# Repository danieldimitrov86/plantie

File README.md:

# Plantie: ESP32 Low-Power Plant Monitor

A complete open-source ecosystem for smart plant monitoring. This project consists of a battery-powered, low-energy **Control Unit** that interfaces with a soil moisture sensor, and a dedicated **Base Station** for charging and data upload.

## 🚧 Project Status

This project is currently under active development.

- [X] **Control Unit:** Hardware Schematics
- [ ] **Control Unit:** PCB Layout
- [ ] **Control Unit:** Firmware
- [ ] **Control Unit:** 3D Printable Enclosure Design
- [X] **Base Station:** Hardware Schematics
- [ ] **Base Station:** PCB Layout
- [ ] **Base Station:** 3D Printable Enclosure Design

## 📂 Repository Structure

```text
.
├── firmware/              # Source code for the ESP32 Control Unit
│   └── control-unit/      # Code for the main module
│
├── hardware/              # PCB Design files (KiCad)
│   ├── base-station/      # (WIP) Schematic & layout for the dock
│   └── control-unit/      # Schematic & layout for the main module
│
└── mechanical/            # (WIP) 3D models for enclosures

```

## ⚖️ License

This project is dual-licensed to accommodate both hardware and software freedoms:

### 🖥️ Software (Firmware)

All code located in the `firmware/` directory is licensed under a [GNU General Public License v3.0 (GPL-3.0)](LICENSE-GPL).

### 🛠️ Hardware (Schematics, PCB, 3D Models)
[![CC BY-SA 4.0][cc-by-sa-shield]][cc-by-sa]

All hardware designs located in the `hardware/` directory are licensed under a
[Creative Commons Attribution-ShareAlike 4.0 International License][cc-by-sa].

[![CC BY-SA 4.0][cc-by-sa-image]][cc-by-sa]

[cc-by-sa]: http://creativecommons.org/licenses/by-sa/4.0/
[cc-by-sa-image]: https://licensebuttons.net/l/by-sa/4.0/88x31.png
[cc-by-sa-shield]: https://img.shields.io/badge/License-CC%20BY--SA%204.0-lightgrey.svg

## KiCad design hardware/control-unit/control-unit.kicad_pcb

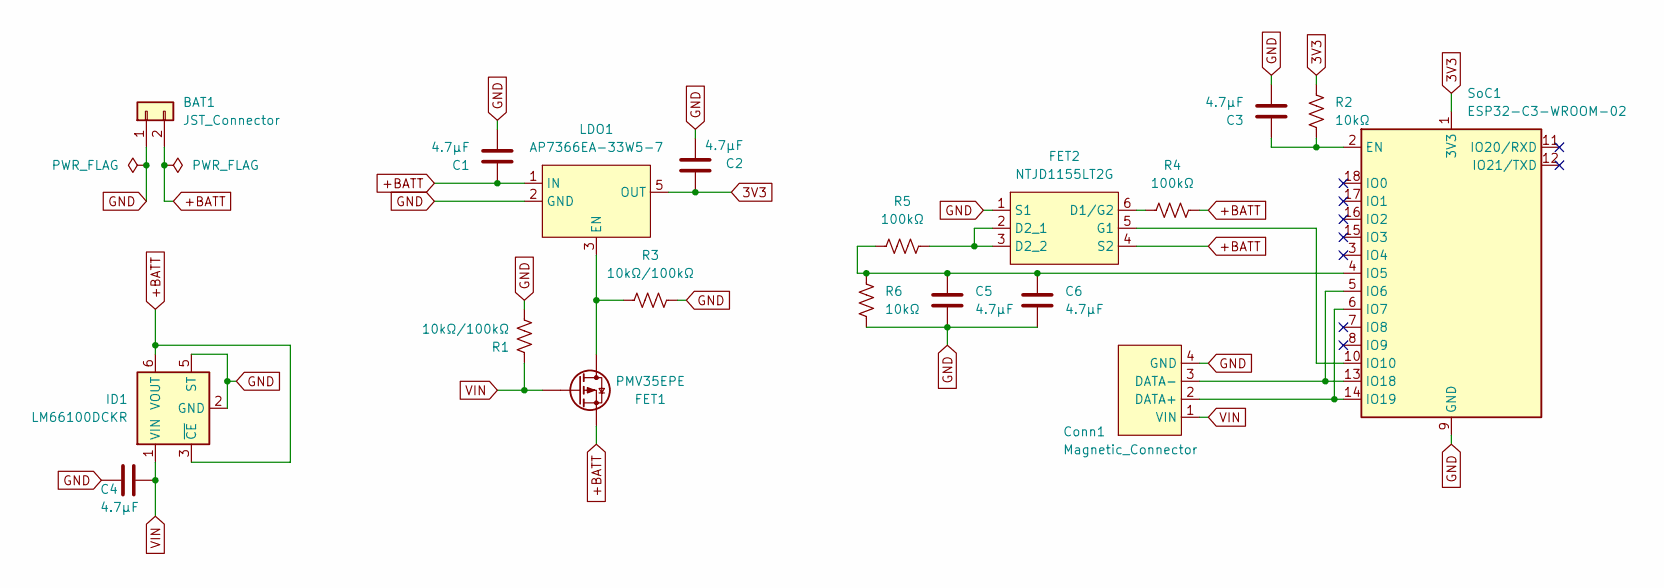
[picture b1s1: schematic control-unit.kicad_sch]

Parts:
BAT1: JST_Connector; JST_EH_B2B-EH-A_1x02_P2.50mm_Vertical
C1, C2, C3, C4, C5, C6: 4.7µF; C_0402_1005Metric_Pad0.74x0.62mm_HandSolder
Conn1: Magnetic_Connector; Connector_Magnetic_4_Pin
FET1: PMV35EPE; SOT-23_Handsoldering
FET2: NTJD1155LT2G; SOT-363_SC-70-6_Handsoldering
ID1: LM66100DCKR; SOT-363_SC-70-6_Handsoldering
LDO1: AP7366EA-33W5-7; SOT-23-5_HandSoldering
R1, R3: 10kΩ/100kΩ; R_0805_2012Metric_Pad1.20x1.40mm_HandSolder
R2, R6: 10kΩ; R_0805_2012Metric_Pad1.20x1.40mm_HandSolder
R4, R5: 100kΩ; R_0805_2012Metric_Pad1.20x1.40mm_HandSolder
SoC1: ESP32-C3-WROOM-02; ESP32-C3-WROOM-02_Handsolder

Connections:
+3.3V: C2.2, LDO1.5 (OUT), R2.2, SoC1.1 (3V3)
+BATT: BAT1.2, C1.2, FET1.2 (S), FET2.4 (S2), ID1.3 (~CE), ID1.6 (VOUT), LDO1.1 (IN), R4.2
GND: BAT1.1, C1.1, C2.1, C3.1, C4.1, C5.1, C6.1, Conn1.4 (GND), FET2.1 (S1), ID1.2 (GND), ID1.5 (ST), LDO1.2 (GND), R1.1, R3.2, R6.1, SoC1.9 (GND), SoC1.19 (GND)
unnamed: Conn1.2 (DATA+), SoC1.6 (IO7), SoC1.14 (IO19)
unnamed: Conn1.3 (DATA-), SoC1.5 (IO6), SoC1.13 (IO18)
unnamed: FET1.3 (D), LDO1.3 (EN), R3.1
unnamed: FET2.6 (D1/G2), R4.1
unnamed: FET2.2 (D2_1), FET2.3 (D2_2), R5.2
unnamed: FET2.5 (G1), SoC1.10 (IO10)
unnamed: C3.2, R2.1, SoC1.2 (EN)
unnamed: C5.2, C6.2, R5.1, R6.2, SoC1.4 (IO5)
VIN: C4.2, Conn1.1 (VIN), FET1.1 (G), ID1.1 (VIN), R1.2

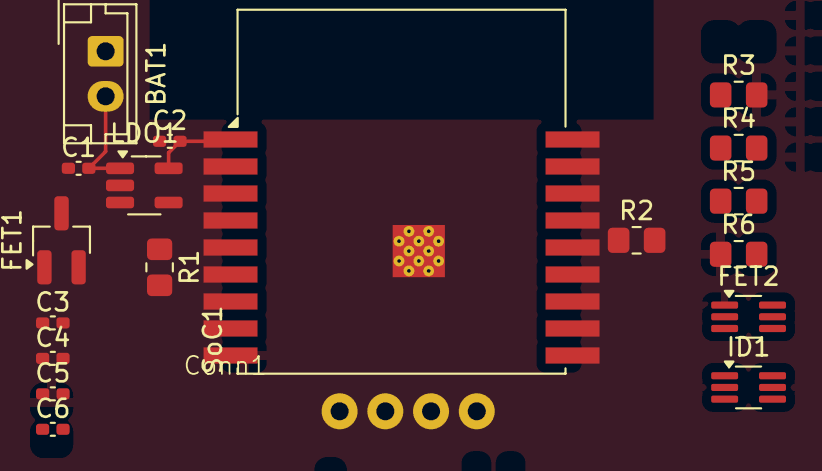
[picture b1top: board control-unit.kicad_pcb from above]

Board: 2 copper layers, 19 parts (0 on the bottom side), 12 nets.

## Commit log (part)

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2025-11-25 Imported KiCad projects for control unit and base station. Added README.md and CC license.
2025-11-25 Fixed README typo
2025-11-25 Renamed magnetic connector symbol. Renamed global labes to use subscripts. Added placeholder resistors and capacitors to USB data pin connections
2025-11-25 Added schematic for base station
2025-11-25 Updated README progress
2025-11-26 Replaced MCP73831T with TPB4056A
2025-11-30 Fixed minor ERC issues on control unit
2025-11-30 Fixed minor ERC issues on base station
2025-11-30 Added missing footprint assignments
2025-12-01 Replaced P-channel FET at LDO EN pin with N-channel

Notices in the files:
README.md:
License: GPL v3
